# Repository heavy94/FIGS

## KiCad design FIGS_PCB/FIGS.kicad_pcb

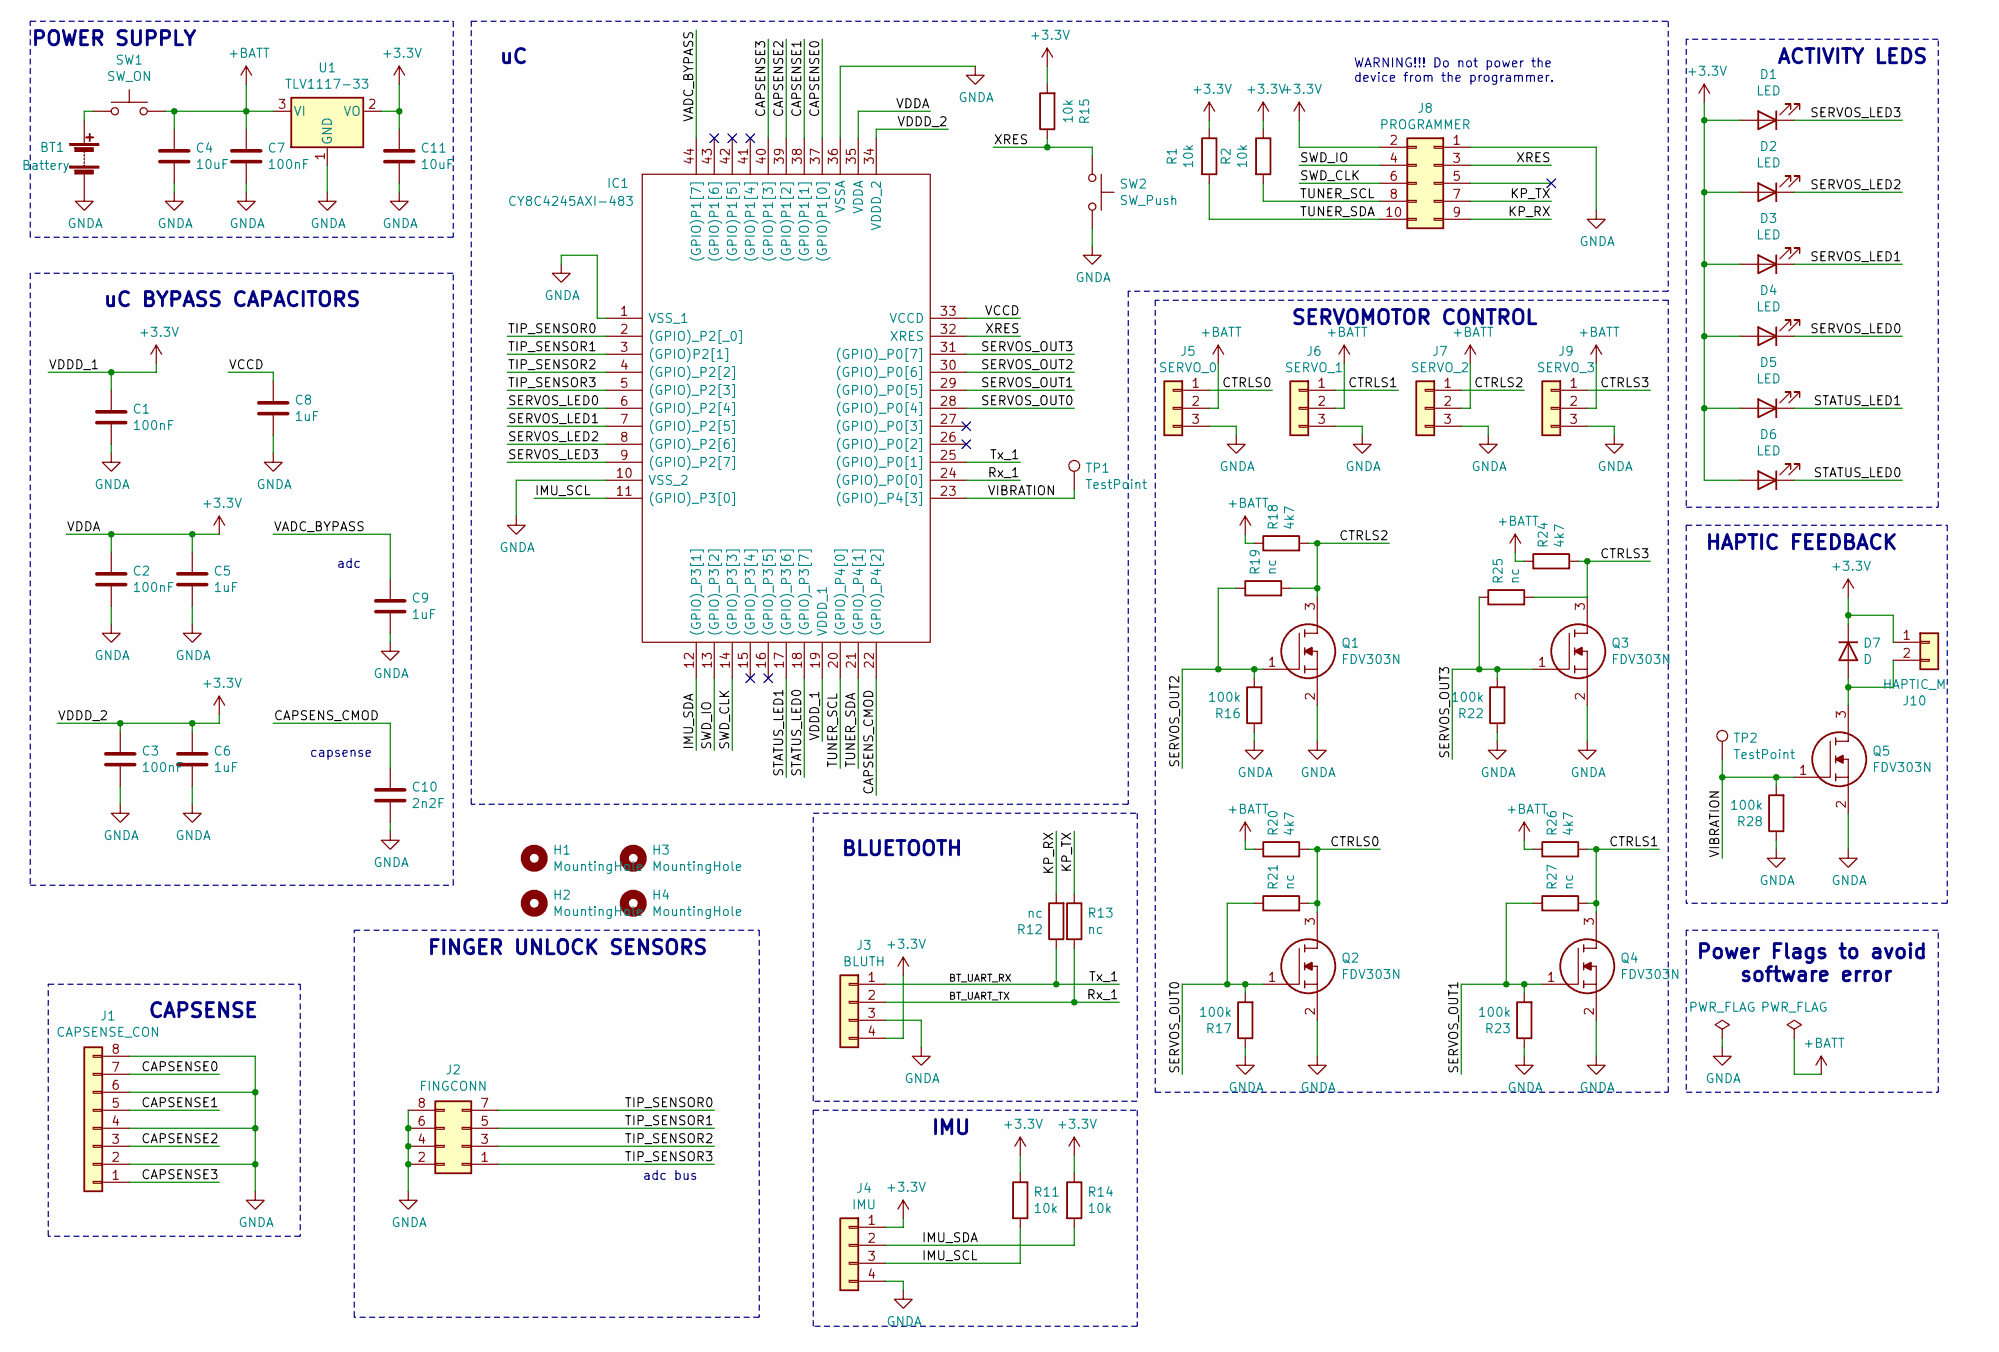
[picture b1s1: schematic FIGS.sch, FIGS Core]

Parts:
BT1: Battery; PinHeader_1x02_P2.54mm_Vertical
C1, C2, C3, C7: 100nF; C_0805_2012Metric_Pad1.18x1.45mm_HandSolder
C4, C11: 10uF; CP_EIA-7132-20_AVX-U_Pad2.72x3.50mm_HandSolder
C5, C6, C8, C9: 1uF; C_0805_2012Metric_Pad1.18x1.45mm_HandSolder
C10: 2n2F; C_0805_2012Metric_Pad1.18x1.45mm_HandSolder
D1, D2, D3, D4, D5, D6: LED; LED_D3.0mm
D7: D; D_MicroMELF_Handsoldering
H1, H2, H3, H4: MountingHole; MountingHole_2.7mm
IC1: CY8C4245AXI-483; QFP80P1200X1200X160-44N; Manufacturer_Part_Number CY8C4245AXI-483; Mouser Part Number 727-CY8C4245AXI-483
J1: CAPSENSE_CON; PinHeader_1x08_P2.54mm_Horizontal
J2: FINGCONN; PinHeader_2x04_P2.54mm_Horizontal
J3: BLUTH; PinHeader_1x04_P2.54mm_Horizontal
J4: IMU; PinHeader_1x04_P2.54mm_Horizontal
J5: SERVO_0; PinHeader_1x03_P2.54mm_Horizontal
J6: SERVO_1; PinHeader_1x03_P2.54mm_Horizontal
J7: SERVO_2; PinHeader_1x03_P2.54mm_Horizontal
J8: PROGRAMMER; PinHeader_2x05_P2.54mm_Vertical
J9: SERVO_3; PinHeader_1x03_P2.54mm_Horizontal
J10: HAPTIC_M; PinHeader_1x02_P2.54mm_Horizontal
Q1, Q2, Q3, Q4, Q5: FDV303N; SOT96P237X111-3N; Manufacturer_Part_Number FDV303N; Mouser Part Number 512-FDV303N
R1, R2, R11, R14, R15: 10k; R_1206_3216Metric_Pad1.30x1.75mm_HandSolder
R12, R13, R19, R21, R25, R27: nc; R_1206_3216Metric_Pad1.30x1.75mm_HandSolder
R16, R17, R22, R23, R28: 100k; R_1206_3216Metric_Pad1.30x1.75mm_HandSolder
R18, R20, R24, R26: 4k7; R_1206_3216Metric_Pad1.30x1.75mm_HandSolder
SW1: SW_ON; SW_CuK_JS202011CQN_DPDT_Straight
SW2: SW_Push; SW_PUSH_6mm_H4.3mm
TP1, TP2: TestPoint; TestPoint_Pad_D3.0mm
U1: TLV1117-33; SOT230P700X180-4N

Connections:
+3V3: C1.1, C2.1, C3.1, C5.1, C6.1, C11.1, D1.2 (A), D2.2 (A), D3.2 (A), D4.2 (A), D5.2 (A), D6.2 (A), D7.1 (K), IC1.19 (VDDD_1), IC1.34 (VDDD_2), IC1.35 (VDDA), J3.4, J4.1, J8.2, J10.1, R1.1, R2.1, R11.1, R14.1, R15.2, U1.2 (VO)
+BATT: C4.1, C7.1, J5.2, J6.2, J7.2, J9.2, R18.1, R20.1, R24.1, R26.1, SW1.2, U1.3 (VI)
/BT_UART_RX: IC1.25 ((GPIO)_P0[1]), J3.1, R12.1
/BT_UART_TX: IC1.24 ((GPIO)_P0[0]), J3.2, R13.2
/CAPSENSE0: IC1.37 ((GPIO)P1[0]), J1.7
/CAPSENSE1: IC1.38 ((GPIO)P1[1]), J1.5
/CAPSENSE2: IC1.39 ((GPIO)P1[2]), J1.3
/CAPSENSE3: IC1.40 ((GPIO)P1[3]), J1.1
/CAPSENS_CMOD: C10.1, IC1.22 ((GPIO)_P4[2])
/CTRLS0: J5.1, Q2.3, R20.2, R21.2
/CTRLS1: J6.1, Q4.3, R26.2, R27.2
/CTRLS2: J7.1, Q1.3, R18.2, R19.2
/CTRLS3: J9.1, Q3.3, R24.2, R25.2
/IMU_SCL: IC1.11 ((GPIO)_P3[0]), J4.3, R11.2
/IMU_SDA: IC1.12 ((GPIO)_P3[1]), J4.2, R14.2
/KP_RX: J8.9, R12.2
/KP_TX: J8.7, R13.1
/SERVOS_LED0: D4.1 (K), IC1.6 ((GPIO)_P2[4])
/SERVOS_LED1: D3.1 (K), IC1.7 ((GPIO)_P2[5])
/SERVOS_LED2: D2.1 (K), IC1.8 ((GPIO)_P2[6])
/SERVOS_LED3: D1.1 (K), IC1.9 ((GPIO)_P2[7])
/SERVOS_OUT0: IC1.28 ((GPIO)_P0[4]), Q2.1, R17.2, R21.1
/SERVOS_OUT1: IC1.29 ((GPIO)_P0[5]), Q4.1, R23.2, R27.1
/SERVOS_OUT2: IC1.30 ((GPIO)_P0[6]), Q1.1, R16.2, R19.1
/SERVOS_OUT3: IC1.31 ((GPIO)_P0[7]), Q3.1, R22.2, R25.1
/STATUS_LED0: D6.1 (K), IC1.18 ((GPIO)_P3[7])
/STATUS_LED1: D5.1 (K), IC1.17 ((GPIO)_P3[6])
/SWD_CLK: IC1.14 ((GPIO)_P3[3]), J8.6
/SWD_IO: IC1.13 ((GPIO)_P3[2]), J8.4
/TIP_SENSOR0: IC1.2 ((GPIO)_P2[_0]), J2.7
/TIP_SENSOR1: IC1.3 ((GPIO)P2[1]), J2.5
/TIP_SENSOR2: IC1.4 ((GPIO)_P2[2]), J2.3
/TIP_SENSOR3: IC1.5 ((GPIO)_P2[3]), J2.1
/TUNER_SCL: IC1.20 ((GPIO)_P4[0]), J8.8, R2.2
/TUNER_SDA: IC1.21 ((GPIO)_P4[1]), J8.10, R1.2
/VADC_BYPASS: C9.1, IC1.44 ((GPIO)P1[7])
/VCCD: C8.1, IC1.33 (VCCD)
/VIBRATION: IC1.23 ((GPIO)_P4[3]), Q5.1, R28.2, TP1.1, TP2.1
/XRES: IC1.32 (XRES), J8.3, R15.1, SW2.1
GNDA: BT1.2 (-), C1.2, C2.2, C3.2, C4.2, C5.2, C6.2, C7.2, C8.2, C9.2, C10.2, C11.2, IC1.1 (VSS_1), IC1.10 (VSS_2), IC1.36 (VSSA), J1.2, J1.4, J1.6, J1.8, J2.2, J2.4, J2.6, J2.8, J3.3, J4.4, J5.3, J6.3, J7.3, J8.1, J9.3, Q1.2, Q2.2, Q3.2, Q4.2, Q5.2, R16.1, R17.1, R22.1, R23.1, R28.1, SW2.2, U1.1 (GND)
unnamed: BT1.1 (+), SW1.1
unnamed: D7.2 (A), J10.2, Q5.3

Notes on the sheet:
FINGER UNLOCK SENSORS
POWER SUPPLY
SERVOMOTOR CONTROL
ACTIVITY LEDS
uC BYPASS CAPACITORS
adc bus
IMU
HAPTIC FEEDBACK
adc
capsense
WARNING!!! Do not power the device from the programmer.
BLUETOOTH
CAPSENSE
Power Flags to avoid software error

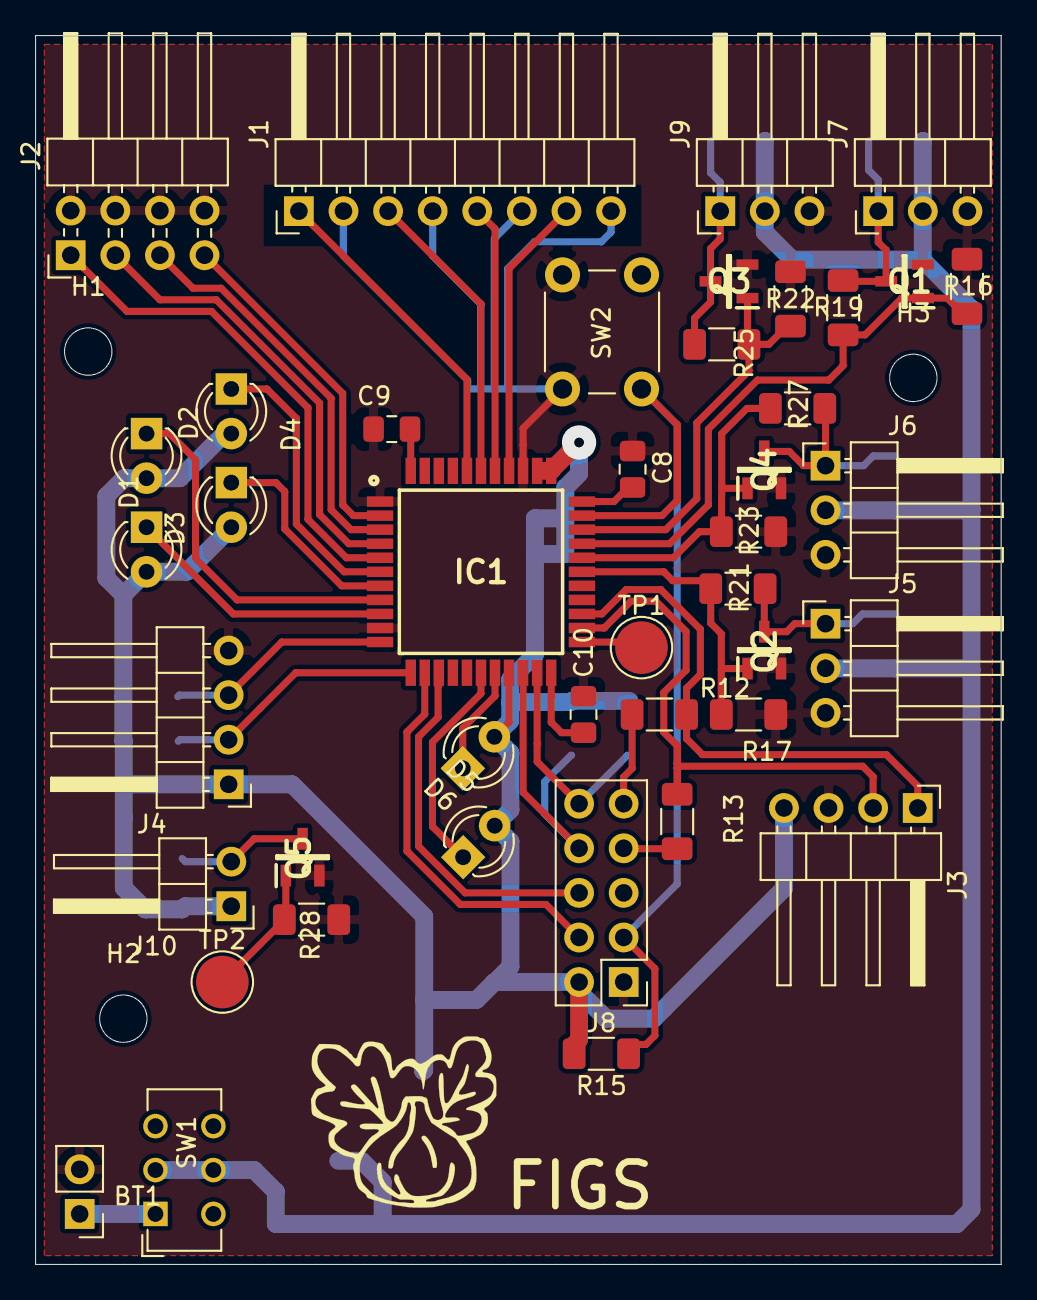
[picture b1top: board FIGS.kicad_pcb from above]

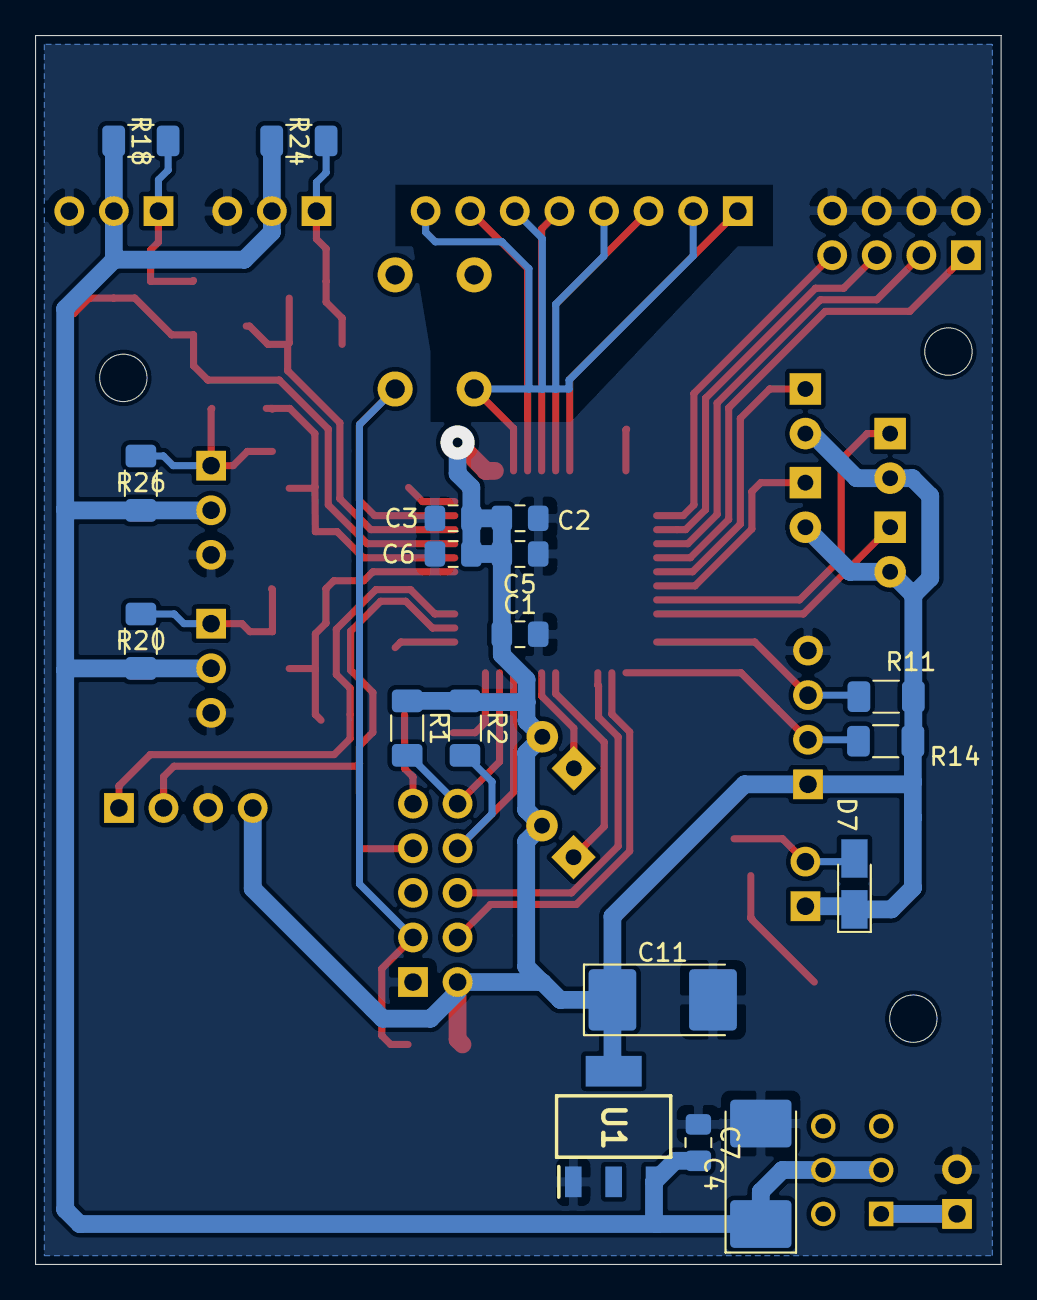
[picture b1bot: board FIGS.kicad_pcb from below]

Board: 2 copper layers, 55.0 x 70.0 mm, 63 parts (18 on the bottom side), 42 nets.

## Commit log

2021-02-15 Initial commit. Capacitive sensing example added
2021-02-18 blender finger movement
2021-02-20 Blender - Python script with finger rotation
2021-02-27 Blender added functionality to print on collision detection
2021-03-01 Added looping function along with sphere and capsule objects
2021-03-01 Hardware configured in PSoC Creator project
2021-03-02 FIGS PCB PROJECT KiCAD
2021-03-02 Schematic modifications
2021-03-02 added uC symbol/lib in project global mylib library and in the folder library
2021-03-03 Mahony filter C
2021-03-03 Filter to remove gyroscope drift
2021-03-04 PCB for FIGS
2021-03-05 PCB changed
2021-03-05 Finished PCB with LOGO and text
2021-03-07 added Pullups on tuner SCL/SDA lines
2021-03-08 IMU code added positioning not proper yet
2021-03-08 I did not make these changes...
2021-03-08 Blender change position of hand wrt angle
2021-03-10 Flowchart and Images committed
2021-03-10 Deleted extra directory FIGS_PSB
2021-03-12 Updated Blender code to send message of proper format
2021-03-15 Changed to right hand
2021-03-15 Right hand model
2021-03-18 last changes
2021-03-18 now here should the f****g sensor data be
2021-03-20 exel book of Capsense data
2021-03-20 wrong test
2021-03-20 IMU tset data
2021-03-20 Capsense test data
2021-03-21 seperated AC/AD/AB in different colums
2021-03-21 seperated AD/AC/AB in different colums for Roll test
